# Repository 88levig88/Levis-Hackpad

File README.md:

# Versity

Versity is a macropad that has 8 keys which are all backlit, a rotary encoder switch, and an OLED display.

## Finished Design:

## Case:

## PCB:

## Schematic:

## Firmware
I used [KMK](https://github.com/KMKfw/kmk_firmware/tree/main). Right now the keys are set to numbers 1-9 and the rotary encoder changes volume, but these are placeholders. I'll update the firmware and take advantage of the OLED screen once I have the case and PCB assembled.

## BOM

Here's all the parts needed:
- 8 x Cherry MX Switches
- 8 x DSA Keycaps
- 3 x M3x16mm screws
- 9 x 1N4148 Diodes
- 12 x SK6812 MINI-E LEDs
- 1 x 0.91" 128x32 OLED Display
- 1 x EC11 Rotary Encoder
- 1 x XIAO RP2040
- 1 x Case (2 x 3D printed parts)

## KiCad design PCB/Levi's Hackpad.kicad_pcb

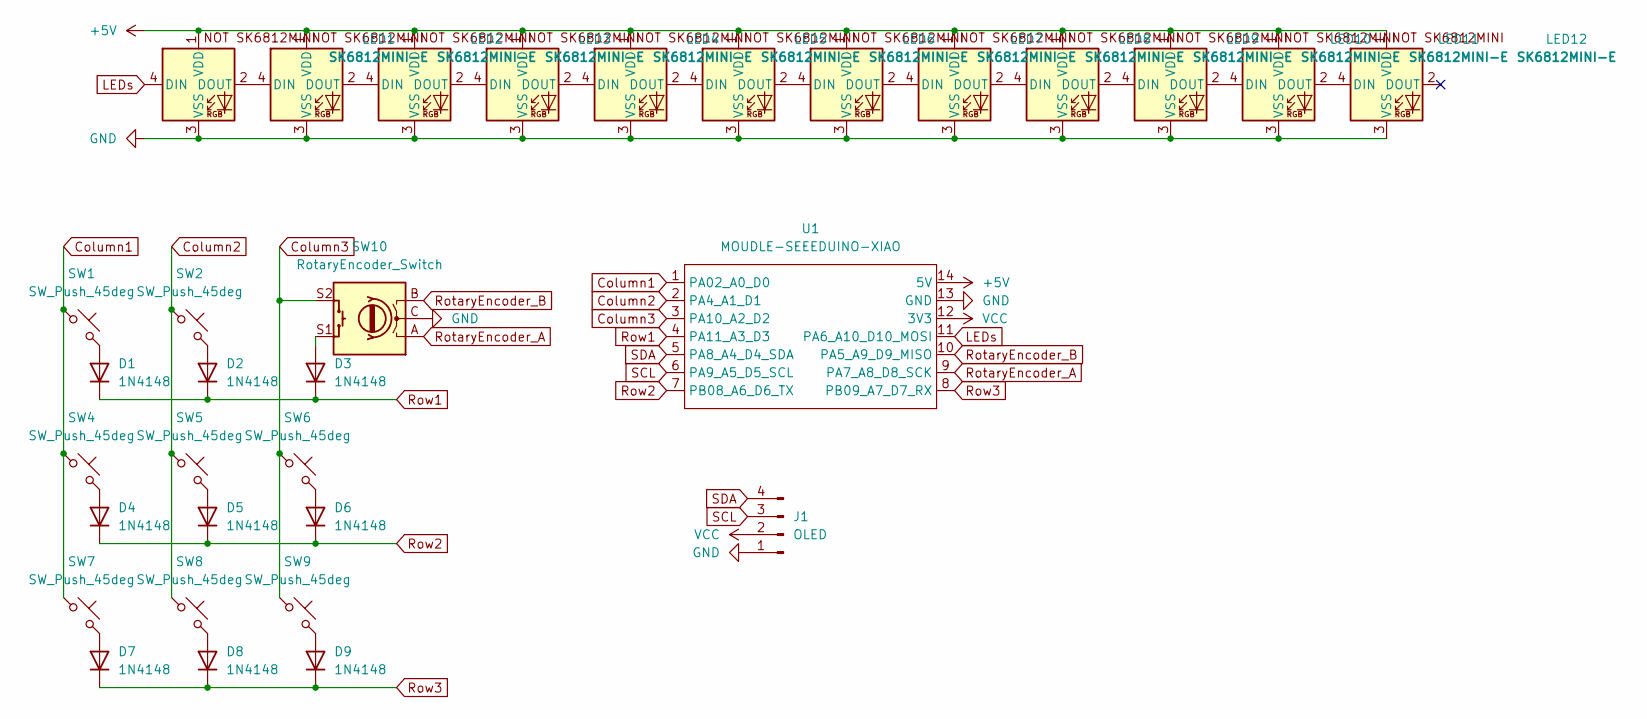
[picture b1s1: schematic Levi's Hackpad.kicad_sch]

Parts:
D1, D2, D3, D4, D5, D6, D7, D8, D9: 1N4148; D_DO-35_SOD27_P7.62mm_Horizontal
J1: OLED; SSD1306-0.91-OLED-4pin-128x32
LED1, LED2, LED3, LED4, LED5, LED6, LED7, LED8, LED9, LED10, LED11, LED12: SK6812MINI-E; SK6812MINI-E_fixed
SW1, SW2, SW4, SW5, SW6, SW7, SW8, SW9: SW_Push_45deg; SW_Cherry_MX_1.00u_PCB
SW10: RotaryEncoder_Switch; RotaryEncoder_Alps_EC11E-Switch_Vertical_H20mm
U1: MOUDLE-SEEEDUINO-XIAO; XIAO-Generic-Hybrid-14P-2.54-21X17.8MM

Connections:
+5V: LED1.1 (VDD), LED2.1 (VDD), LED3.1 (VDD), LED4.1 (VDD), LED5.1 (VDD), LED6.1 (VDD), LED7.1 (VDD), LED8.1 (VDD), LED9.1 (VDD), LED10.1 (VDD), LED11.1 (VDD), LED12.1 (VDD), U1.14 (5V)
Column1: SW1.1, SW4.1, SW7.1, U1.1 (PA02_A0_D0)
Column2: SW2.1, SW5.1, SW8.1, U1.2 (PA4_A1_D1)
Column3: SW6.1, SW9.1, SW10.S2, U1.3 (PA10_A2_D2)
GND: J1.1, LED1.3 (VSS), LED2.3 (VSS), LED3.3 (VSS), LED4.3 (VSS), LED5.3 (VSS), LED6.3 (VSS), LED7.3 (VSS), LED8.3 (VSS), LED9.3 (VSS), LED10.3 (VSS), LED11.3 (VSS), LED12.3 (VSS), SW10.C, U1.13 (GND)
LEDs: LED1.4 (DIN), U1.11 (PA6_A10_D10_MOSI)
unnamed: D1.2 (A), SW1.2
unnamed: D2.2 (A), SW2.2
unnamed: D3.2 (A), SW10.S1
unnamed: D4.2 (A), SW4.2
unnamed: D5.2 (A), SW5.2
unnamed: D6.2 (A), SW6.2
unnamed: D7.2 (A), SW7.2
unnamed: D8.2 (A), SW8.2
unnamed: D9.2 (A), SW9.2
unnamed: LED1.2 (DOUT), LED2.4 (DIN)
unnamed: LED2.2 (DOUT), LED3.4 (DIN)
unnamed: LED3.2 (DOUT), LED4.4 (DIN)
unnamed: LED4.2 (DOUT), LED5.4 (DIN)
unnamed: LED5.2 (DOUT), LED6.4 (DIN)
unnamed: LED6.2 (DOUT), LED7.4 (DIN)
unnamed: LED7.2 (DOUT), LED8.4 (DIN)
unnamed: LED8.2 (DOUT), LED9.4 (DIN)
unnamed: LED9.2 (DOUT), LED10.4 (DIN)
unnamed: LED10.2 (DOUT), LED11.4 (DIN)
unnamed: LED11.2 (DOUT), LED12.4 (DIN)
RotaryEncoder_A: SW10.A, U1.9 (PA7_A8_D8_SCK)
RotaryEncoder_B: SW10.B, U1.10 (PA5_A9_D9_MISO)
Row1: D1.1 (K), D2.1 (K), D3.1 (K), U1.4 (PA11_A3_D3)
Row2: D4.1 (K), D5.1 (K), D6.1 (K), U1.7 (PB08_A6_D6_TX)
Row3: D7.1 (K), D8.1 (K), D9.1 (K), U1.8 (PB09_A7_D7_RX)
SCL: J1.3, U1.6 (PA9_A5_D5_SCL)
SDA: J1.4, U1.5 (PA8_A4_D4_SDA)
VCC: J1.2, U1.12 (3V3)

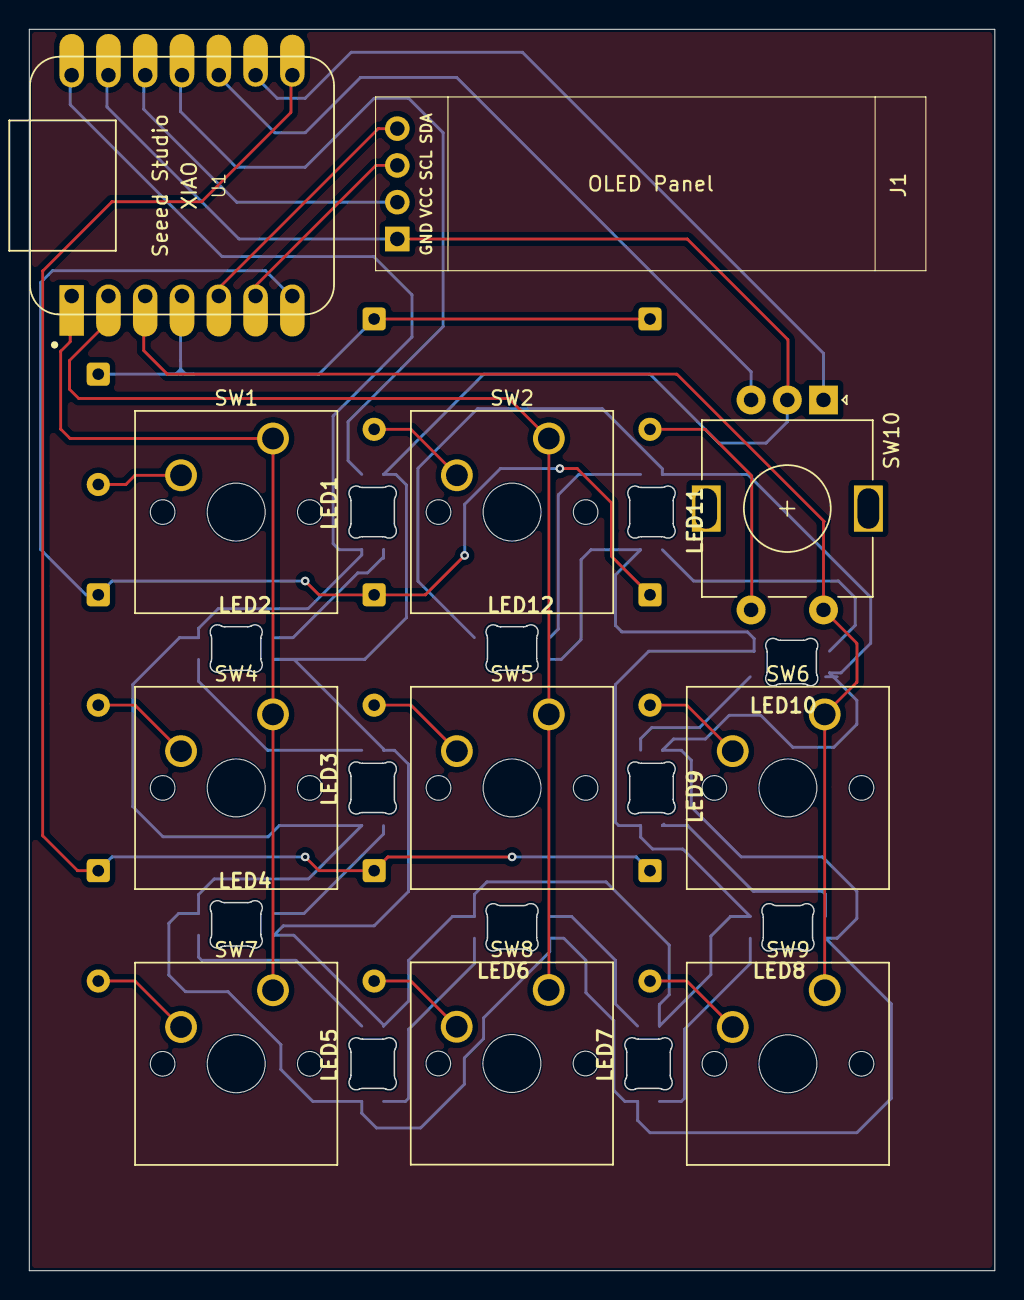
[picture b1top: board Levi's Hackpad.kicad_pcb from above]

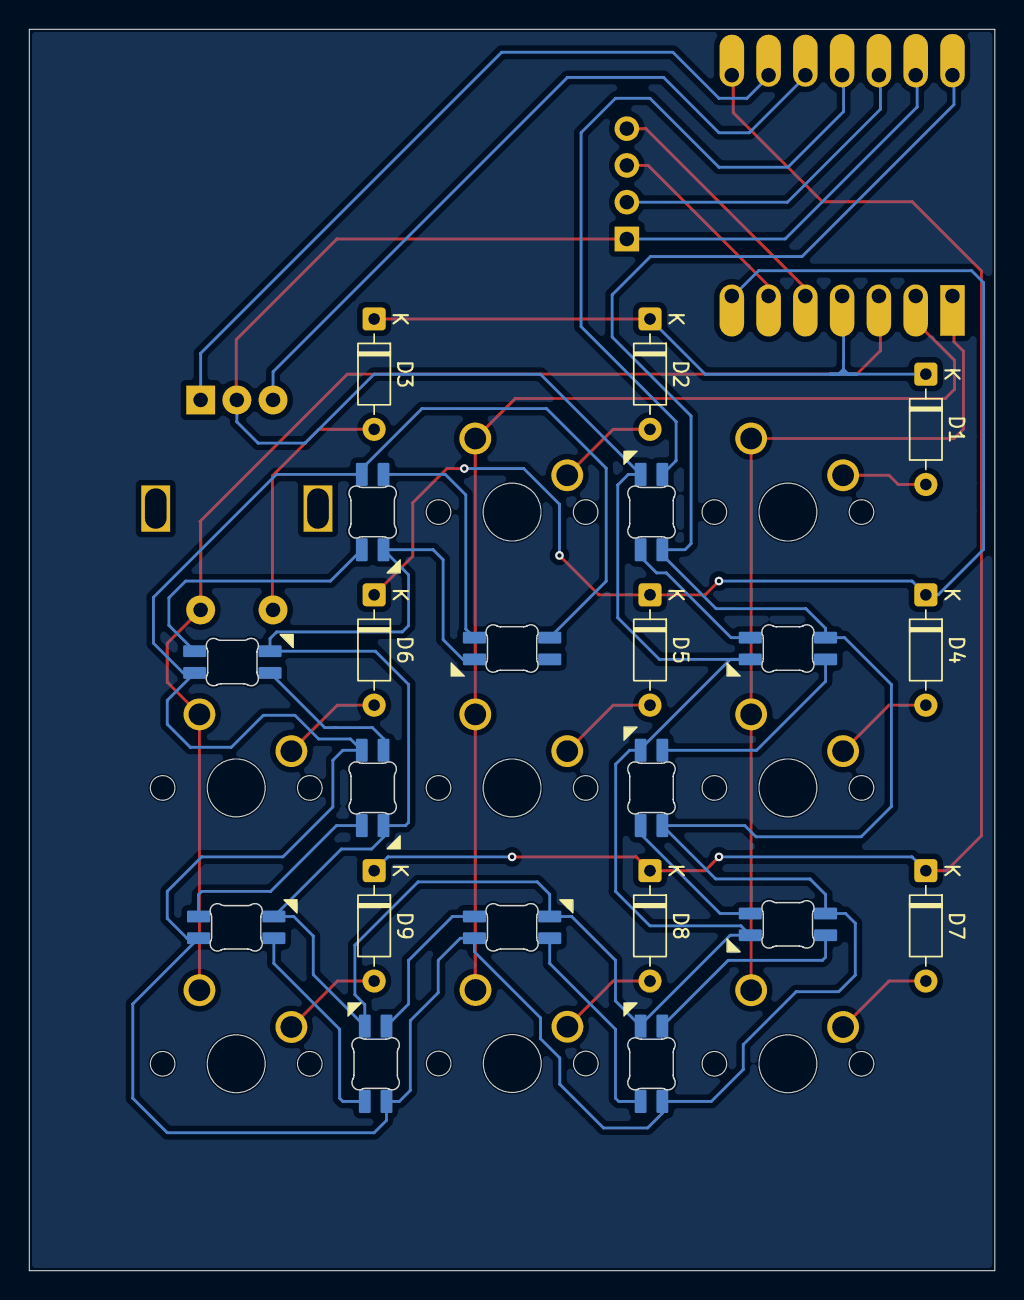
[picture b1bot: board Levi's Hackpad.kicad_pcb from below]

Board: 2 copper layers, 66.7 x 85.7 mm, 32 parts (9 on the bottom side), 34 nets.
